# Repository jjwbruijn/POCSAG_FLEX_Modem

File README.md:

# POCSAG/FLEX Modem

A complete project for receiving pager data, and transmitting POCSAG/FLEX data to old pagers.

Caution:
 - TX: Please only use with a dummy load on HAM-bands
 - RX: Please don't look at data you're not supposed to receive

## Parts required:
- 78M05
- AMS1117-33
- TTGO-T-display ESP32 module
- RF4463F30 module
- Some passives
optional:
- A relay to drive an external PA
- Status LEDS's

## How it works
The modem uses a RF4463F30 wireless module (NiceRF) https://www.tindie.com/products/nicerf/rf4463f30-1w-wireless-transceiver-module/ . Inside is an Silicon Labs Si4463 and a PA, and you can use it to broadcast pretty far-ish. Haven't checked the output yet, but it is a pretty cheap module and you may need to add output filters to avoid splatter on other frequencies. The module allows frequencies up to 1050 Mhz, this should cover (nearly?) all pager bands. While the modules may be optimized for specific frequency bands, they will happily transmit outside of their optimum band. Range will be severly reduced though. 

The modem supports:
- POCSAG 512
- POCSAG 1200
- POCSAG 2400
- FLEX 1600
- FLEX 3200/2
- FLEX 3200/4
- FLEX 6400/4

Technically the module should be capable of transmitting ERMES data too; I haven't implemented this due to the absence of any working ERMES networks, and I don't have any ERMES pagers in my collection. I'd love to implement ReFLEX (two way paging), but I can't find ANY relevant data/protocol info. There's some stuff in Motorola patents, but it's hard to find anything meaningful.

POCSAG is easy and straightforward; it's not synchronized and the pagers listen regularly. The length of the POCSAG preamble is pretty long, and the pagers will happily sync and receive info. They will display a little antenna symbol if they don't see any pager traffic for some time. 

The Motorola FLEX protocol is a synchronous protocol; this has a major drawback: if a pager is sync'ed to your network, it will remain synced until it times out, not receiving a couple of frames. 
This means: 
- If you reset your modem (or if it crashes), your pager will probably lose sync. New messages sent will probably not be received by your pager. You could fix this with a GPS receiver with a PPS output, but it has not been implemented yet.
- FLEX pagers do expect a fair amount of traffic. If they don't regularly see traffic in their assigned frames, they will lose sync and usually default to listening until they get synced up to the network again. This will drain your battery rather quickly!

To help keep pagers happy, the modem will regularly send empty/idle frames on frequencies/frames that have been used to send messages to pagers.

The modem is capable of syncing-up to existing FLEX pager networks, and send on their frequencies, in their timeslots. I've never tested this, and neither should you.

## How to use
- Build the board
- Build/upload firmware and filesystem
- Connect to wifi (The board will run as an AP, connect and enter your wifi details
- Point your browser to the IP shown on the display, enter frequencies (in Hz) and data, and send away!

For RX purposes there's somewhat of a web-interface, at <ip>/index.html, but you'll need to fill in the IP address of the device in main.js. [this is what it looks like](https://user-images.githubusercontent.com/2544995/197303511-72ad286d-d64b-4eff-b078-07b176b526e7.png)
)

## Adding Frequencies
The RF4463 in the modem uses config files generated by the WDS utility ( https://www.silabs.com/documents/login/software/WDS3-Setup.exe ) 
Click 'Simulate Radio', and select the Radio Configuration Application for the RF4463. You can use the included XML templates as a starting point, just add the frequency and hit 'Generate source'. Name it following the naming convention used by the other files in the folder, and use the included php-file to generate a rfconfig.h-styled file to use in the firmware.

Note: Not all frequencies need to be added; if you entered the channel spacing correctly, the firmware will find the channel based on the base frequency setting and spacing.

## Tips and tricks
- POCSAG uses 'function' bits A through D to distinguish between different types of messages, but these are mostly to be used on 'tone' pagers. Most numeric pagers expect A, most alphanumeric pagers expect D, and will decode A-coded messages as numeric. Some pagers support folders, and use different function values to sort messages
- Some pagers use special sequences to do OTA configuration. If you ever find out what those sequences are for popular models, please let me know.
- While they're really supposed to, not all FLEX pagers support all FLEX modes. Some only support the 2FSK modes.

## Limitations
- It basically hogs an entire ESP32 core during transmission; this is because everything is pretty time-critical
- It's not amazingly stable
- Firmware uses poor, unsafe coding practices. There's probably a ton of memory leaks :)
- Multi-phase FLEX RX on US nation-wide networks will crash the ESP32 pretty fast. I haven't had an awful lot of time to bugfix this, but the firmware isn't too happy to see a ton of traffic

## Disclaimer
- I absolutely deny any and all responsibility should you chose to use, sell, lend or loan, or even just look at this software or hardware design. It's not fit for public consumption, and probably not suitable to be used by anyone. You're on your own!

## Errata
- The original version has GPIO2 connected to one of the GPIO's on the RF module. For some reason, this causes an issue where the RF module does something weird during boot. Not sure. Just don't connect the ESP32 GPIO2 pin to the main board and you're good.
- The RF4463 needs to be calibrated for proper use. Calibrated value is set in RF4463.cpp at or around line #288. Should be around that value, calibrating it will improve your range by better matching your pager. Haven't found a better way to do it than just transmitting and checking the resulting frequency using an SDR RX

## TODO
- Code cleanup
- Web interface
- Web interface
- I am once again asking for a web interface

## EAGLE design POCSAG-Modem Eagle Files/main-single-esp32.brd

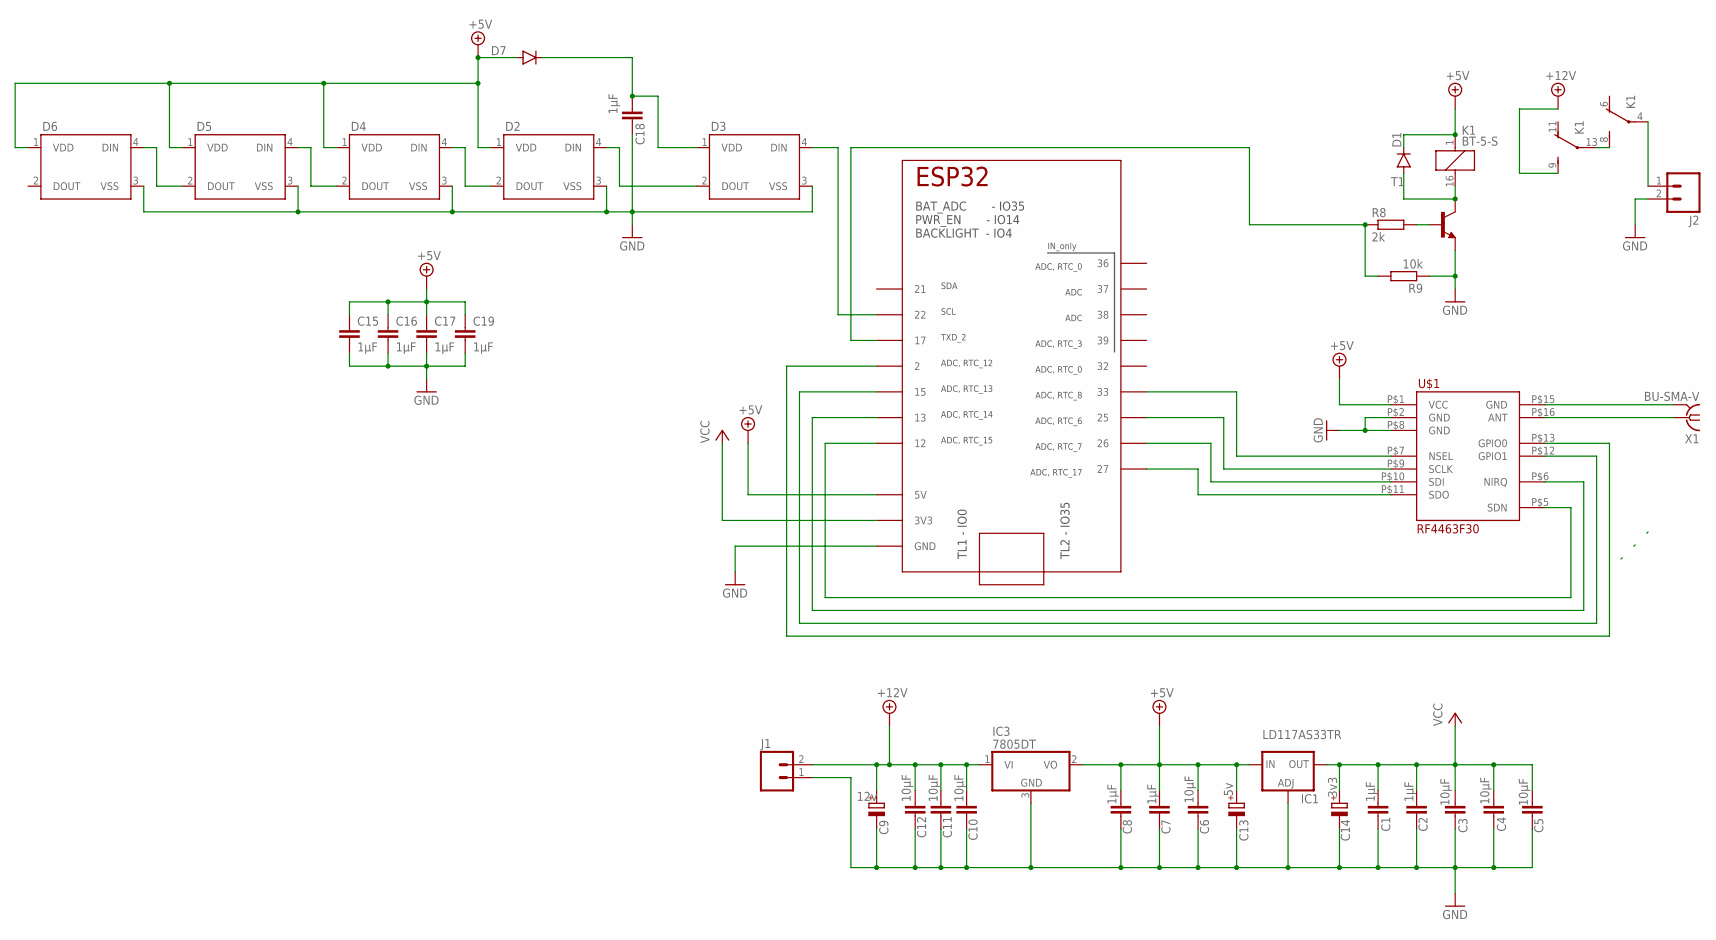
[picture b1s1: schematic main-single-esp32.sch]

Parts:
C1, C2, C7, C8: 1µF; C1206K
C3, C4, C5, C6, C10, C11, C12: 10µF; C1206K
C9: 12v; D/7343-31W
C13: 5v; D/7343-31W
C14: 3v3; D/7343-31W
C15, C16, C17, C18, C19: 1µF; C0805
D1, D7: DIODESMA; SMA-DIODE
D2, D3, D4, D5, D6: WS2812B
IC1: LD117AS33TR; SOT223
IC2: TTGO_DISP; TTGO_DISP_DEFAULT
IC3: 7805DT; TO252
J1, J2: M023.5MM-NO_SILK; SCREWTERMINAL-3.5MM-2-NS
K1: BT-5-S; BT-XX-S
R8: 2k; R1206
R9: 10k; R1206
T1: MMBT2222ALT1-NPN-SOT23-BEC; SOT23-BEC
U$1: RF4463F30; NICERF_16PIN_SPI_TRANSCEIVER
X1: BU-SMA-V

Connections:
+5V: C6.1, C7.1, C8.1, C13.+, C15.1, C16.1, C17.1, C19.1, D1.C, D2.1 (VDD), D4.1 (VDD), D5.1 (VDD), D6.1 (VDD), D7.A, IC1.3 (IN), IC2.5V, IC3.2 (VO), K1.1, U$1.P$1 (VCC)
+12V: C9.+, C10.1, C11.1, C12.1, IC3.1 (VI), J1.2, K1.9 (S)
GND: C1.2, C2.2, C3.2, C4.2, C5.2, C6.2, C7.2, C8.2, C9.-, C10.2, C11.2, C12.2, C13.-, C14.-, C15.2, C16.2, C17.2, C18.2, C19.2, D2.3 (VSS), D3.3 (VSS), D4.3 (VSS), D5.3 (VSS), D6.3 (VSS), IC1.1 (ADJ), IC2.GND_1 (GND), IC2.GND_2 (GND), IC2.GND_3 (GND), IC2.GND_4 (GND), IC2.GND_5 (GND), IC3.3 (GND), J1.1, J2.2, R9.1, T1.E, U$1.P$2 (GND), U$1.P$8 (GND)
unnamed: IC2.27, U$1.P$11 (SDO)
unnamed: IC2.26, U$1.P$10 (SDI)
unnamed: IC2.25, U$1.P$9 (SCLK)
unnamed: U$1.P$16 (ANT), X1.1
unnamed: U$1.P$15 (GND), X1.2, X1.3 (2), X1.4 (2), X1.5 (2)
unnamed: IC2.33, U$1.P$7 (NSEL)
unnamed: IC2.12, U$1.P$5 (SDN)
unnamed: R8.2, T1.B
unnamed: D2.4 (DIN), D3.2 (DOUT)
unnamed: D1.A, K1.16 (2), T1.C
unnamed: IC2.13, U$1.P$6 (NIRQ)
unnamed: IC2.15, U$1.P$12 (GPIO1)
unnamed: IC2.2, U$1.P$13 (GPIO0)
unnamed: IC2.17, R8.1, R9.2
unnamed: D2.2 (DOUT), D4.4 (DIN)
unnamed: D4.2 (DOUT), D5.4 (DIN)
unnamed: D5.2 (DOUT), D6.4 (DIN)
unnamed: K1.8 (S), K1.13
unnamed: J2.1, K1.4
unnamed: D3.4 (DIN), IC2.22
unnamed: C18.1, D3.1 (VDD), D7.C
VCC: C1.1, C2.1, C3.1, C4.1, C5.1, C14.+, IC1.4 (OUT), IC2.3V3_1 (3V3), IC2.3V3_2 (3V3)

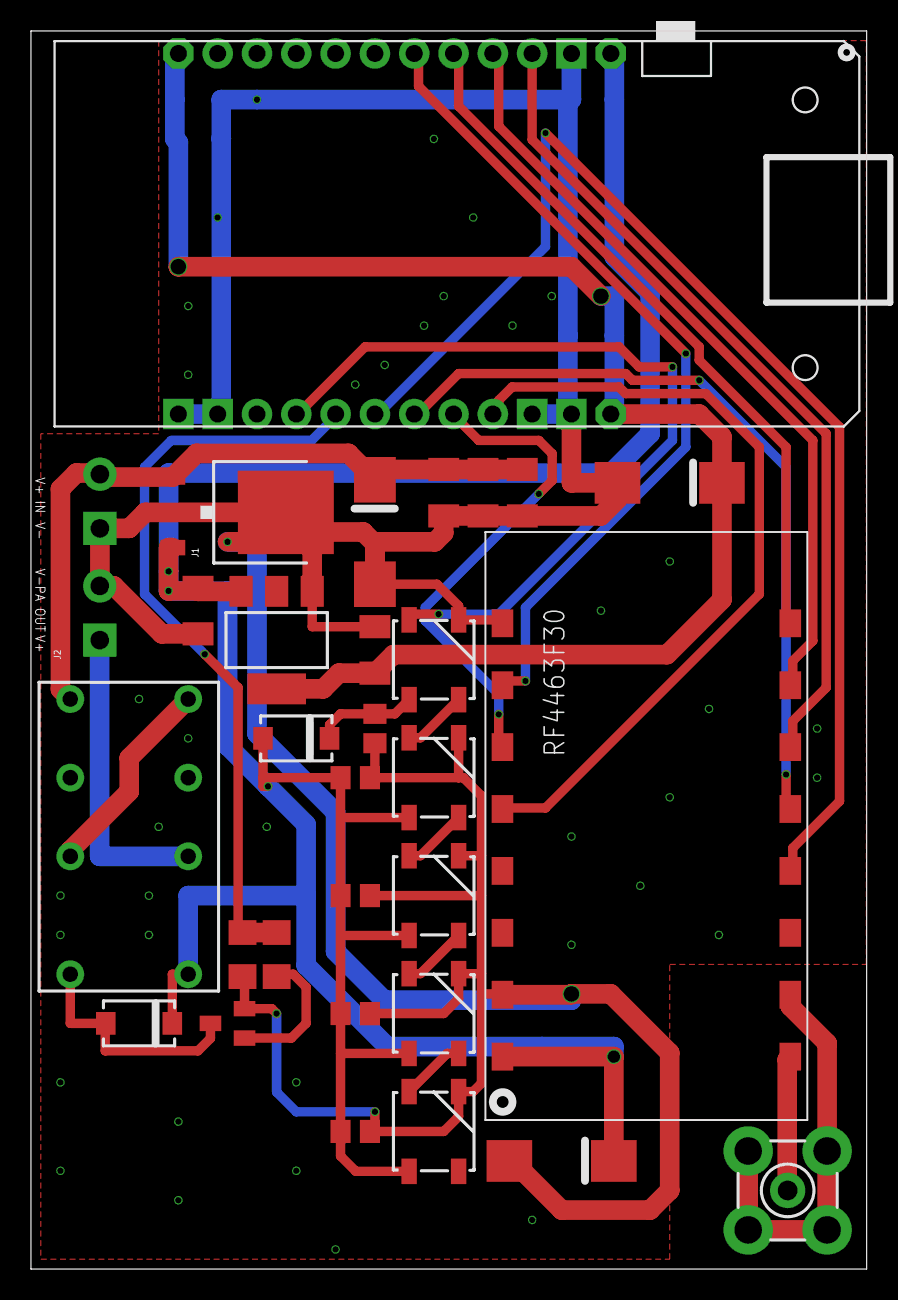
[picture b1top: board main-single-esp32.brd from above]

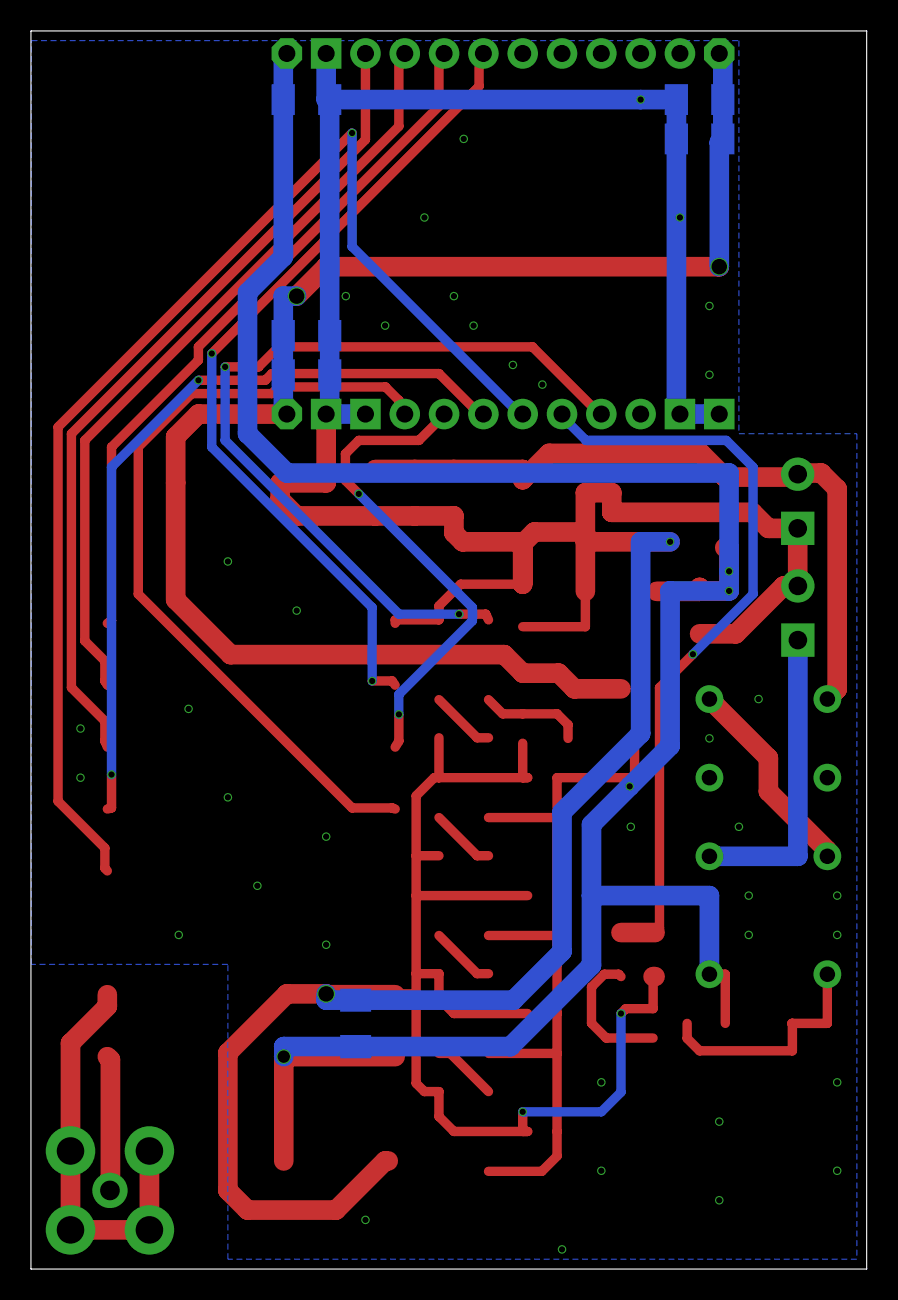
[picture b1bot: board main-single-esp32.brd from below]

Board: 2 copper layers, 54.0 x 80.0 mm, 37 parts (6 on the bottom side), 25 nets.

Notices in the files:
parts and their libraries:
SparkFun-DiscreteSemi: Licensing: Creative Commons ShareAlike 4.0 International - https://creativecommons.org/licenses/by-sa/4.0
